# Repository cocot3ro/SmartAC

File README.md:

# SmartAC

>[!WARNING]
>This repository is archived and will be continued on my [Codeberg account](https://codeberg.org/cocot3ro/SmartAC).

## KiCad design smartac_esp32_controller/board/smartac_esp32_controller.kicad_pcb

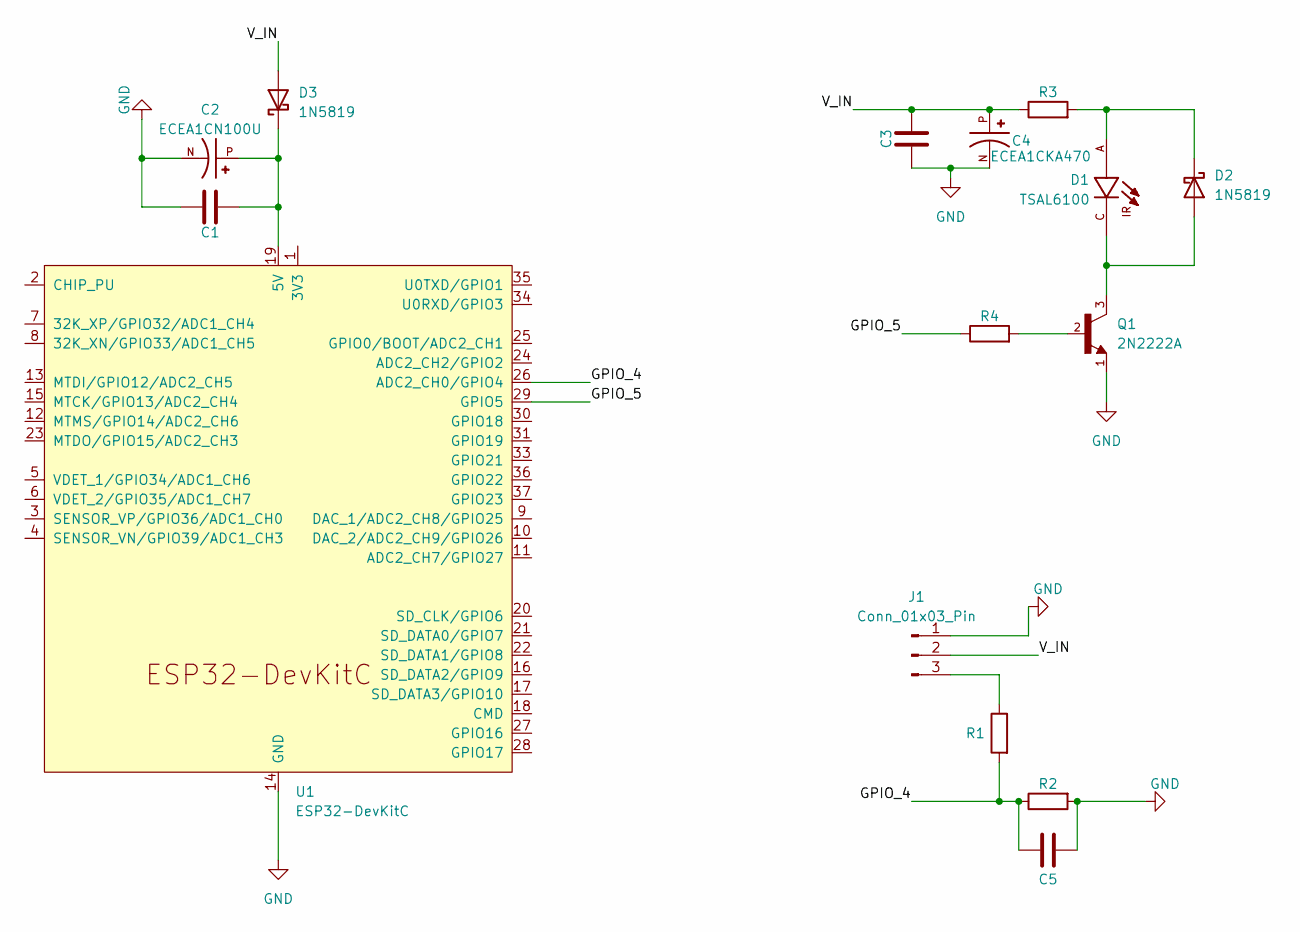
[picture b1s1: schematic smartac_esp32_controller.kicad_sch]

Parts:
C1, C3: C; C_Disc_D4.7mm_W2.5mm_P5.00mm
C2: ECEA1CN100U; CAPPRD200W50D500H1100; PARTREV 28-FEB-20
C4: ECEA1CKA470; CAPPRD200W45D500H700; PARTREV 28-FEB-20
C5: C; CAPRB500W50L400T250H550
D1: TSAL6100; LEDRD254W55D595H900; PARTREV 1.8
D2, D3: 1N5819; D_DO-41_SOD81_P10.16mm_Horizontal
J1: Conn_01x03_Pin; JST_PH_B3B-PH-K_1x03_P2.00mm_Vertical
Q1: 2N2222A; TO92254P470H750-3; PARTREV N/A
R1, R2, R3, R4: R; R_Axial_DIN0207_L6.3mm_D2.5mm_P10.16mm_Horizontal
U1: ESP32-DevKitC

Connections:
/GPIO_4: C5.2, R1.2, R2.1, U1.26 (ADC2_CH0/GPIO4)
/GPIO_5: R4.1, U1.29 (GPIO5)
/V_IN: C3.2, C4.P, D3.2 (A), J1.2, R3.1
GND: C1.1, C2.N, C3.1, C4.N, C5.1, J1.1, Q1.1, R2.2, U1.14 (GND), U1.32 (GND), U1.38 (GND)
unnamed: D1.C, D2.2 (A), Q1.3
unnamed: D1.A, D2.1 (K), R3.2
unnamed: C1.2, C2.P, D3.1 (K), U1.19 (5V)
unnamed: J1.3, R1.1
unnamed: Q1.2, R4.2

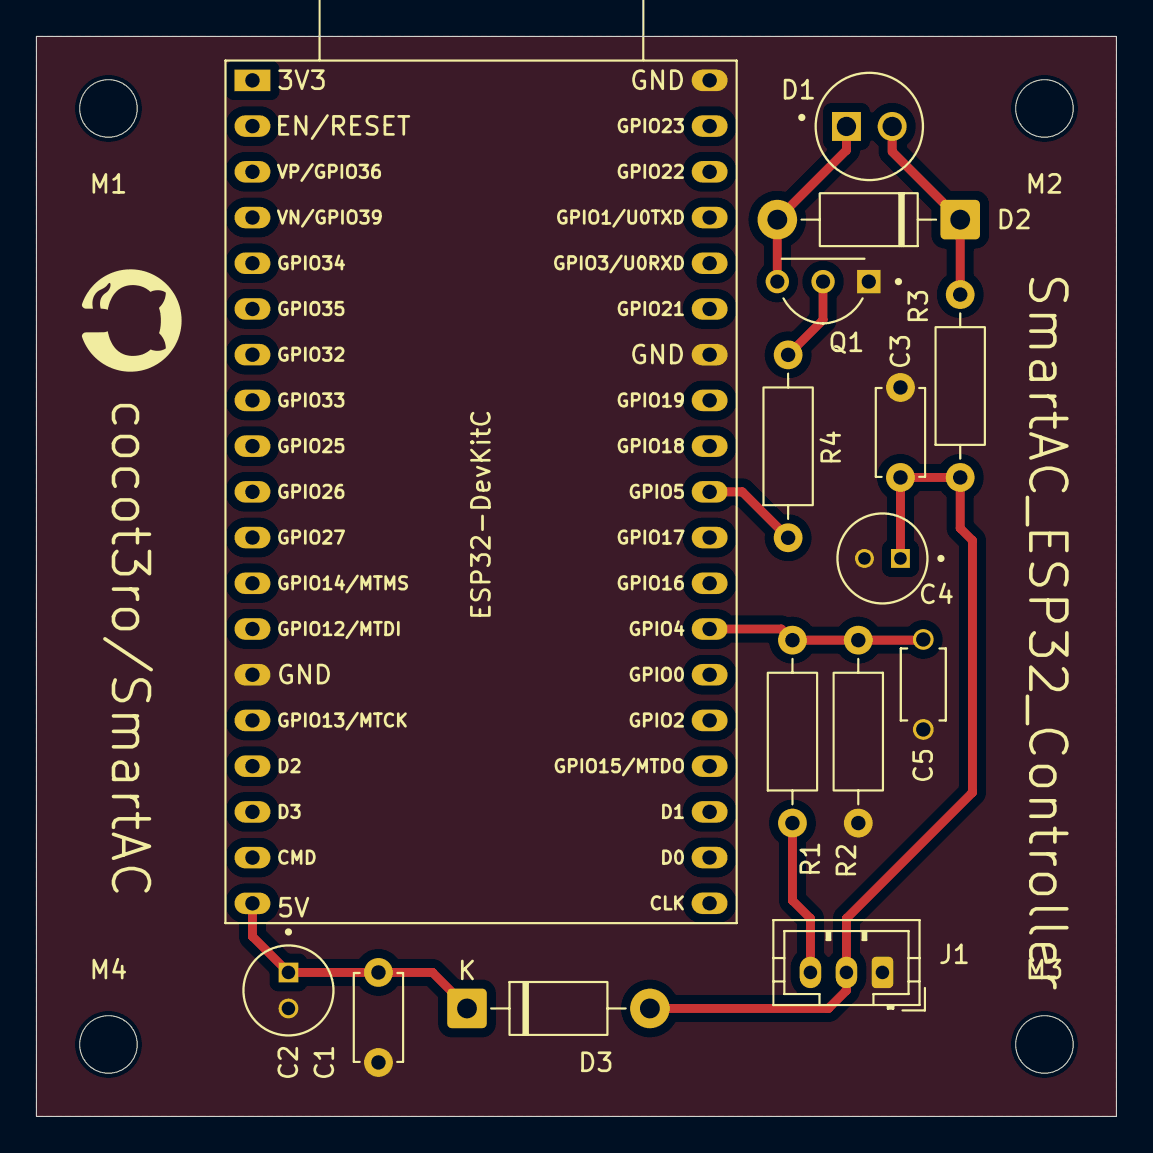
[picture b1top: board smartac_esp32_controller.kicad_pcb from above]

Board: 2 copper layers, 60.0 x 60.0 mm, 19 parts (0 on the bottom side), 9 nets.

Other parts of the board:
M1, M2, M3, M4: MountingHole_3.2mm_M3

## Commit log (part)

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2025-11-08 Remaping GPIOs: 16 -> 4, 17 -> 5
2025-11-08 Changed GPIO
2025-11-08 Basic UART reader for AC display
2025-11-25 utils
2025-11-25 SmartAC board
2025-11-25 SmartAC ESP32 firmware v1
2026-01-16 Nuevo topic 'smartac/status' para estado online/offline. Autoreconexión a la WIFI y MQTT.
2026-01-21 Changed mqtt broker
2026-01-24 Server ok
2026-01-24 Android app. Start and stop the websocket connection according to the lifecycle. Datastore cache
2026-01-26 Some UI refactor
2026-02-14 Android app, UI and dependency updates
    Refactored the floating action button into a multi-level menu for fan speed and AC mode controls.
    Added new icons for different AC modes (Cool, Heat, Fan, Dry).
    Introduced a new UI section to display the current mode and fan speed.
    Updated app dependencies, including Koin, Kotlin, and Compose.
    Switched Koin from KSP to the Koin compiler plugin.
    Enabled API key authentication for the HTTP client.
2026-02-14 Fix Dockerfile
2026-05-23 Renamed old app folder
2026-05-23 Base project with dependencies
2026-05-27 Add AndroidX Navigation3 and Lifecycle dependencies
2026-05-30 Renamed old firmware folder
2026-05-30 New base project for esp32 controller
2026-05-30 Upgrade gradle wrapper to 9.5.1
